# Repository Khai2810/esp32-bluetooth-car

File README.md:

# BluetoothCar Project

## Overview
The BluetoothCar project is designed for the ESP32 microcontroller, enabling Bluetooth functionality to control a car remotely. This project serves as a foundation for building a Bluetooth-controlled car, allowing for further enhancements and customizations.

## Project Structure
```
BluetoothCar
├── platformio.ini
├── src
│   └── main.cpp
├── lib
├── include
├── test
└── README.md
```

## Setup Instructions
1. **Install PlatformIO**: Ensure you have PlatformIO installed in your development environment.
2. **Clone the Repository**: Clone this repository to your local machine.
3. **Open the Project**: Open the `BluetoothCar` folder in PlatformIO.
4. **Install Dependencies**: Run the command to install any required libraries specified in `platformio.ini`.

## Usage
- Connect the ESP32 to your computer and upload the code from `src/main.cpp`.
- Use a Bluetooth-enabled device (like a smartphone) to connect to the ESP32.
- Control the car using the provided Bluetooth commands.

## Contributing
Feel free to fork the repository and submit pull requests for any improvements or features you would like to add.

## License
This project is licensed under the MIT License. See the LICENSE file for more details.

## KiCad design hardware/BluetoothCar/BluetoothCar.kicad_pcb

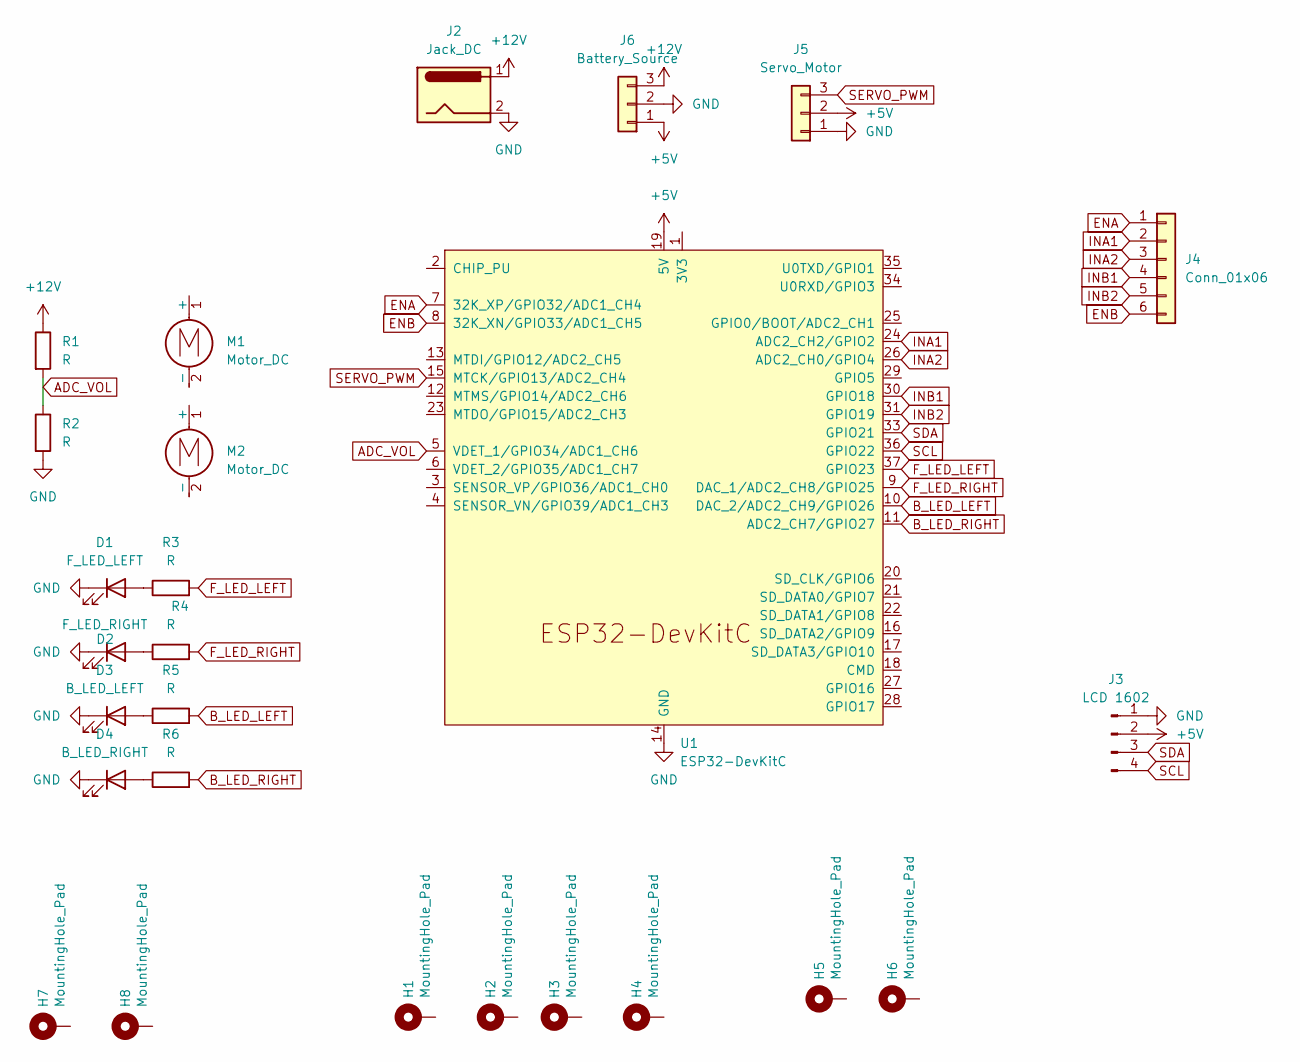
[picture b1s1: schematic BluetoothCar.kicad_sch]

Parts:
D1: F_LED_LEFT; LED_D3.0mm_Horizontal_O1.27mm_Z2.0mm
D2: F_LED_RIGHT; LED_D3.0mm_Horizontal_O1.27mm_Z2.0mm
D3: B_LED_LEFT; LED_D3.0mm_Horizontal_O1.27mm_Z2.0mm
D4: B_LED_RIGHT; LED_D3.0mm_Horizontal_O1.27mm_Z2.0mm
H1, H2, H3, H4, H5, H6: MountingHole_Pad; MountingHole_3mm_Pad
H7, H8: MountingHole_Pad; MountingHole_4.3mm_M4_ISO7380_Pad
J2: Jack_DC; BarrelJack_GCT_DCJ200-10-A_Horizontal
J3: LCD 1602; PinHeader_1x04_P2.54mm_Vertical
J4: Conn_01x06; JST_XH_B6B-XH-A_1x06_P2.50mm_Vertical
J5: Servo_Motor; JST_XH_B3B-XH-A_1x03_P2.50mm_Vertical
J6: Battery_Source; JST_XH_B3B-XH-A_1x03_P2.50mm_Vertical
M1, M2: Motor_DC
R1, R2, R3, R4, R5, R6: R; R_0805_2012Metric
U1: ESP32-DevKitC; MODULE_ESP32-DEVKITC-32D

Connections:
+5V: J3.2, J5.2, J6.1, U1.19 (5V)
+12V: J2.1, J6.3, R1.1
ADC_VOL: R1.2, R2.1, U1.5 (VDET_1/GPIO34/ADC1_CH6)
B_LED_LEFT: R5.2, U1.10 (DAC_2/ADC2_CH9/GPIO26)
B_LED_RIGHT: R6.2, U1.11 (ADC2_CH7/GPIO27)
ENA: J4.1, U1.7 (32K_XP/GPIO32/ADC1_CH4)
ENB: J4.6, U1.8 (32K_XN/GPIO33/ADC1_CH5)
F_LED_LEFT: R3.2, U1.37 (GPIO23)
F_LED_RIGHT: R4.2, U1.9 (DAC_1/ADC2_CH8/GPIO25)
GND: D1.1 (K), D2.1 (K), D3.1 (K), D4.1 (K), J2.2, J3.1, J5.1, J6.2, R2.2, U1.14 (GND), U1.32 (GND), U1.38 (GND)
INA1: J4.2, U1.24 (ADC2_CH2/GPIO2)
INA2: J4.3, U1.26 (ADC2_CH0/GPIO4)
INB1: J4.4, U1.30 (GPIO18)
INB2: J4.5, U1.31 (GPIO19)
unnamed: D1.2 (A), R3.1
unnamed: D2.2 (A), R4.1
unnamed: D3.2 (A), R5.1
unnamed: D4.2 (A), R6.1
SCL: J3.4, U1.36 (GPIO22)
SDA: J3.3, U1.33 (GPIO21)
SERVO_PWM: J5.3, U1.15 (MTCK/GPIO13/ADC2_CH4)

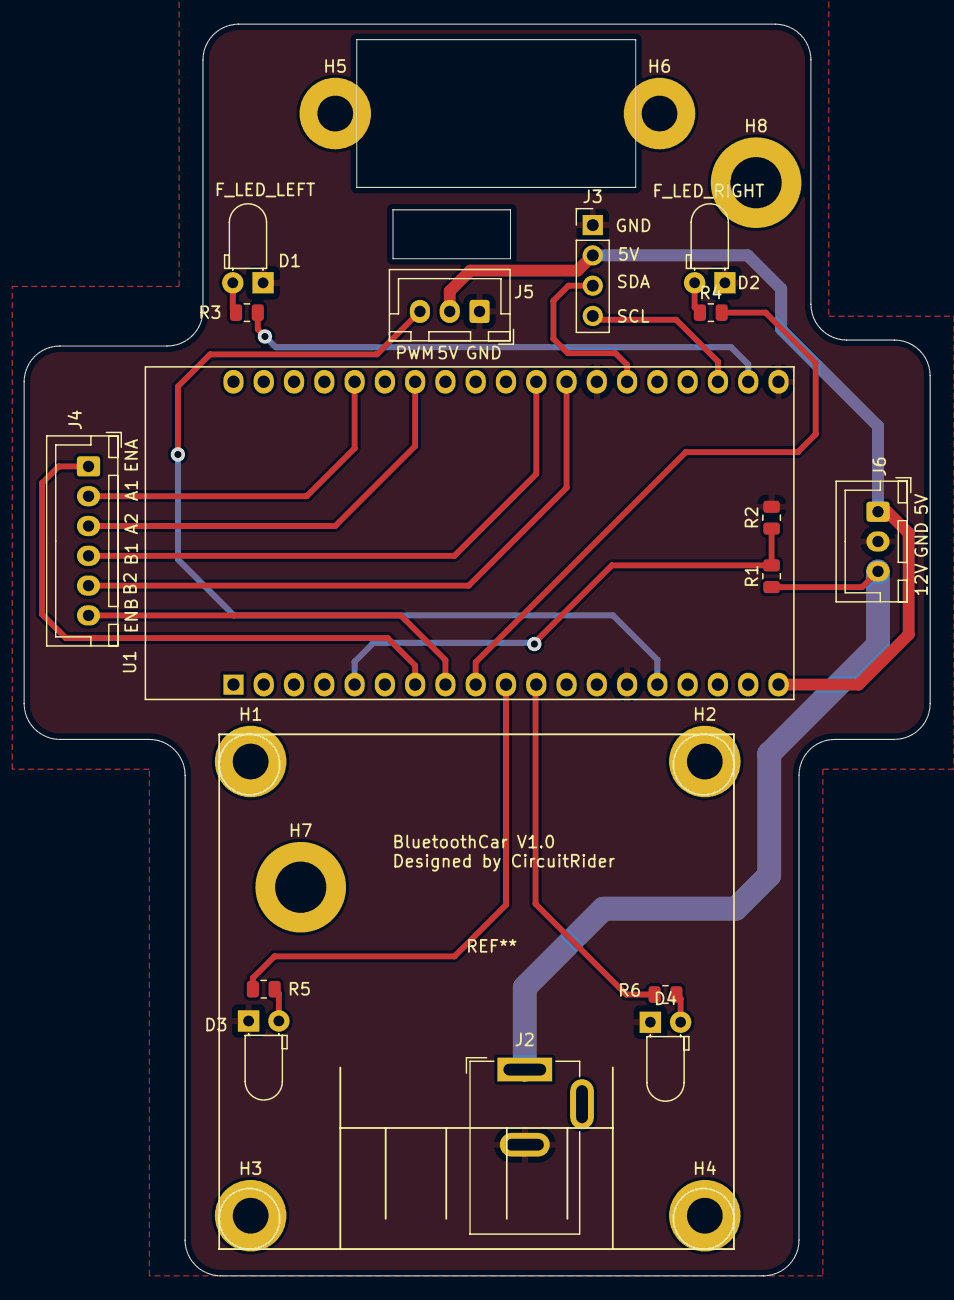
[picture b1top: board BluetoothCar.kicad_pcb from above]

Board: 2 copper layers, 76.0 x 105.0 mm, 24 parts (0 on the bottom side), 21 nets.

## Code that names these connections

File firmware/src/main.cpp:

#include <Arduino.h>
#include <BluetoothSerial.h>
#include "MotorControl.h" // Include the motor header
#include "MotorDC.h"      // Include the motor header
#include "MotorApp.h"     // Include the motor header
#include "Command.h"
#include <BLEDevice.h>
#include <BLEUtils.h>
#include <BLEServer.h>

// BluetoothSerial SerialBT;
#define INA1 4
#define INA2 2
#define ENA 33
#define PWMCHANEL0 0

#define INB1 18
#define INB2 19
#define ENB 32
#define PWMCHANEL1 1
MotorDC motorLeft(ENB, INB1, INB2, PWMCHANEL1);
MotorDC motorRight(ENA, INA1, INA2, PWMCHANEL0);

#define SERVICE_UUID "4fafc201-1fb5-459e-8fcc-c5c9c331914b"
#define CHARACTERISTIC_UUID "beb5483e-36e1-4688-b7f5-ea07361b26a8"

MotorApp car(motorLeft, motorRight);

unsigned char buffer[BUFFER_SIZE];
CircleBuffer circleBuffer(buffer);

std::string receiveByte;
uint8_t type;
uint8_t intensity;

volatile bool hasNewData = false;

class MyCallbacks : public BLECharacteristicCallbacks
{
  void onWrite(BLECharacteristic *pCharacteristic) override
  {
    std::string value = pCharacteristic->getValue();

    if (value.empty())
      return;

    // Copy an toàn sang string ASCII
    receiveByte.assign(value.begin(), value.end());
    hasNewData = true;
  }
};

Command command(circleBuffer);

void HandleCommand()
{
  if (!command.ValidatePackage())
  {
    return;
  }
  package_t frame = command.ReturnFrame();
  // AA 00 01
  if (frame.command == FORWARD)
  {
    car.MoveForward();
  }
  else if (frame.command == REVERSE)
  {
    car.MoveBackward();
  }
}

void ParseSpeed(const char *cmd, uint8_t &type, uint8_t &intensity)
{
  if (cmd == nullptr || cmd[0] == '\0')
  {
    type = 0;
    intensity = 0;
    return;
  }

  type = cmd[0];
  intensity = 0;

  for (int i = 1; cmd[i] >= '0' && cmd[i] <= '9'; i++)
  {
    intensity = intensity * 10 + (cmd[i] - '0');
  }

  if (intensity > 100)
    intensity = 100;
  intensity *= 2;
}

void ControlMotor()
{
  if (!hasNewData)
    return;
  hasNewData = false;

  ParseSpeed(receiveByte.c_str(), type, intensity);

  Serial.print("Type: ");
  Serial.println((char)type);
  Serial.print("Intensity: ");
  Serial.println(intensity);

  if (type == 'T')
  {
    if (intensity > 100)
      car.MoveRight();
    else if (intensity < 100)
      car.MoveLeft();
    else
    {
      car.Stop();
    }
  }
  else if (type == 'G')
  {
    if (intensity == 0)
      car.Stop();
    else if (intensity == 2)
      car.MoveBackward();
    else if (intensity == 6)
      car.MoveForward();
  }
  else if (type == 'S')
  {
    car.SetSpeed(intensity);
  }
}

void setup()
{
  Serial.begin(115200);
  Serial.println("Starting BLE work!");

  BLEDevice::init("MyESP32");

  BLEServer *pServer = BLEDevice::createServer();

  BLEService *pService = pServer->createService(SERVICE_UUID);

  BLECharacteristic *pCharacteristic = pService->createCharacteristic(
      CHARACTERISTIC_UUID,
      BLECharacteristic::PROPERTY_READ |
          BLECharacteristic::PROPERTY_WRITE);

  // Gán callback
  pCharacteristic->setCallbacks(new MyCallbacks());

  pCharacteristic->setValue("Hello World says ESP32");

  pService->start();

  BLEAdvertising *pAdvertising = BLEDevice::getAdvertising();
  pAdvertising->addServiceUUID(SERVICE_UUID);
  pAdvertising->setScanResponse(true);
  pAdvertising->setMinPreferred(0x06);
  pAdvertising->setMinPreferred(0x12);
  BLEDevice::startAdvertising();

  Serial.println("BLE ready! Waiting for data...");
}

void loop()
{
  ControlMotor();
  delay(5);
}

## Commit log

2026-01-09 Bluetooth Car V1.0
2026-01-28 commit model B
2026-02-03 Modify ln298 channel b
